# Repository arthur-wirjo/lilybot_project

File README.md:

## Lilybot: Omnidirectional Robot with LiDAR-Based Navigation

A custom omnidirectional mobile robot combining ESP32-S3 firmware, micro-ROS, and ROS 2 Nav2 for autonomous indoor navigation.

## Overview

Lilybot is a personal robotics project built to explore the full stack of an autonomous robot from scratch, from mechanical design and PCB design to embedded motor control and ROS 2 navigation.

The original motivation was simple: I wanted to build a small "smart walking table" that could help carry items around, such as bringing water or transporting cooking utensils to my dorm pantry. More importantly, this project became a way for me to learn how to build a complete autonomous robot system myself instead of only working on isolated parts.

The robot uses an ESP32-S3 for low-level control and sensing, and a Raspberry Pi 5 for higher-level ROS 2 tasks such as LiDAR processing, SLAM, localization, and navigation.

---

## Key Features

- Custom omnidirectional chassis
- Custom PCB integrating microcontroller, IMU, motor control, and encoder interfaces
- ESP32-S3-based embedded motor control firmware
- IMU and encoder feedback
- Feedforward control using a 1D lookup table with linear interpolation
- PID wheel speed control
- micro-ROS integration between ESP32-S3 and ROS 2
- LiDAR-based SLAM and Nav2 navigation on Raspberry Pi 5

---

## Hardware

### Main Components

- **Motor:** PG36-3650 geared BLDC motor, 12V rated, 1:50 reduction
- **Wheels:** Generic 75 mm omnidirectional wheels
- **IMU:** MPU6050
- **Computer:** Raspberry Pi 5 running Ubuntu 24.04
- **LiDAR:** RPLIDAR C1
- **Microcontroller:** ESP32-S3 Development Board (N16R8 variant)
- **Battery 1:** Generic 3S Li-Po battery
- **Power Distribution Board:** Generic 12V PDB with 5V output for ESP32
- **Battery 2:** Generic power bank dedicated to Raspberry Pi 5

### Custom PCB

The custom PCB includes:

- ESP32-S3 microcontroller
- IMU
- motor control outputs
- encoder feedback inputs
- two TXS0108E bidirectional level shifters

The level shifters are used because the ESP32 operates at 3.3V logic while the motor interfaces operate at 5V logic.

---

## Note on the Motor Choice

The motors used in this project are inexpensive geared BLDC motors with built-in motor drivers and encoder feedback. They are convenient for prototyping, but the velocity response is noticeably nonlinear under PWM control.

A simple PID controller alone was too slow and resulted in noticeable drift. Adding feedforward improved the response, but drift remained, especially at certain velocity ranges. I also tried a 2nd-order feedforward model with PID, which improved things further but was still not consistent enough across the full operating range.

To address this, I wrote a motor testing program to measure steady-state motor speed at different PWM duty cycles, plotted the results in a spreadsheet, and converted the data into a 1D lookup table. Linear interpolation was then used between table entries to generate the feedforward term. Combined with PID feedback, this gave the most satisfactory real-world performance.

---

## System Architecture

The system is split into two computing layers.

### ESP32-S3

The ESP32-S3 handles low-level real-time tasks:

- encoder reading
- IMU reading
- motor control loop
- odometry calculation
- micro-ROS communication
- publishing odometry-related data
- subscribing to commanded velocity data

### Raspberry Pi 5

The Raspberry Pi 5 handles high-level ROS 2 tasks:

- ROS 2 nodes
- LiDAR reading
- SLAM and localization
- Nav2 planning and control

---

## RTOS Task Structure

To keep the firmware more reliable and responsive, the ESP32-S3 uses both cores for separate responsibilities.

### Core 0: Real-Time Control

Core 0 is dedicated to the low-level control loop. Its tasks include:

- reading encoder pulse counts
- calculating odometry
- converting robot velocity targets into individual wheel targets
- running feedforward + PID wheel speed control
- updating PWM outputs to the motors

### Core 1: Communication and Sensors

Core 1 handles communication-heavy and less timing-critical tasks:

- running the micro-ROS executor
- receiving `cmd_vel` commands
- reading IMU data
- publishing IMU and odometry messages to ROS 2 over UART

This separation helped keep the control loop more stable while still maintaining communication with the Raspberry Pi.

---

## Setup

These instructions assume the Raspberry Pi 5 is running Ubuntu 24.04 and development is done over SSH.

### 1. Clone the Repository

```bash
cd ~
git clone https://github.com/arthur-wirjo/lilybot_project.git
```

---

### 2. Install ESP-IDF

Lilybot firmware is developed using ESP-IDF.

Install prerequisites:

```bash
sudo apt-get update
sudo apt-get install git wget flex bison gperf python3 python3-venv cmake ninja-build ccache libffi-dev libssl-dev dfu-util libusb-1.0-0
```

Clone ESP-IDF:

```bash
mkdir -p ~/esp
cd ~/esp
git clone -b v6.0.2 --recursive https://github.com/espressif/esp-idf.git
```

Install the toolchain:

```bash
cd ~/esp/esp-idf
./install.sh esp32
```

Export the environment:

```bash
. $HOME/esp/esp-idf/export.sh
```

Optionally, add this alias to `~/.bashrc` for convenience:

```bash
alias get_idf='. $HOME/esp/esp-idf/export.sh'
```

Then reload:

```bash
source ~/.bashrc
```

---

### 3. Flash the ESP32-S3 Firmware

In one terminal:

```bash
cd ~/lilybot_project/firmware_esp32s3/micro-ROS
idf.py flash monitor
```

---

### 4. Run the micro-ROS Agent

In another terminal:

```bash
cd ~/lilybot_project/firmware_esp32s3
docker run -it --rm -v /dev:/dev --privileged --net=host microros/micro-ros-agent:jazzy serial --dev /dev/ttyAMA0 -b 115200
```

Alternatively:

```bash
./run_microros_agent.sh
```

---

### 5. Build the ROS 2 Workspace

In another terminal:

```bash
cd ~/lilybot_project/ros2_ws
colcon build
```

---

### 6. Run the ROS 2 Stack

The main setup commands are:

```bash
ros2 launch my_robot_description rsp.launch.py
ros2 run foxglove_bridge foxglove_bridge
ros2 launch sllidar_ros2 sllidar_c1_launch.py serial_port:=/dev/ttyUSB0
ros2 run robot_localization ekf_node --ros-args --params-file src/lilybot_localization/config/ekf.yaml
ros2 launch slam_toolbox online_async_launch.py slam_params_file:=src/lilybot_localization/config/mapper_params.yaml
ros2 launch nav2_bringup bringup_launch.py use_sim_time:=False autostart:=True map:=src/lilybot_navigation/dorm_map.yaml params_file:=src/lilybot_navigation/config/custom_nav2_params.yaml
ros2 run nav2_map_server map_saver_cli -f src/lilybot_navigation/dorm_map
```

Additional setup commands are documented in the repository.

---

## Implementation Notes

This project was built solo, including:

- mechanical design
- PCB design
- embedded firmware
- control implementation
- ROS 2 integration
- robot assembly and testing

---

## Challenges and Lessons Learned

### Nonlinear Motor Behavior

One of the main challenges was achieving stable and consistent wheel speed control using low-cost motors with nonlinear PWM-to-speed behavior.

The progression was roughly:

1. PID only  
2. feedforward + PID  
3. 2nd-order feedforward + PID  
4. 1D lookup table feedforward + PID

The lookup-table-based feedforward gave the best results in practice.

### Noisy Encoder-Derived Odometry

Encoder-based odometry was noisier than expected, especially due to the characteristics of the motors and drivetrain. This made low-pass filtering important for producing more stable velocity and odometry estimates.

### Multi-Core Task Separation

Using both ESP32 cores helped keep the real-time motor control loop more reliable while offloading communication and sensor publishing to the other core.

### PCB Design Retrospective

Looking back with more hardware experience from my later DIY FOC controller project, I would have used a ground copper pour instead of manually routing ground traces point-to-point. In this case the board was simple and low power, so it still worked acceptably, but it was still not the best layout practice.

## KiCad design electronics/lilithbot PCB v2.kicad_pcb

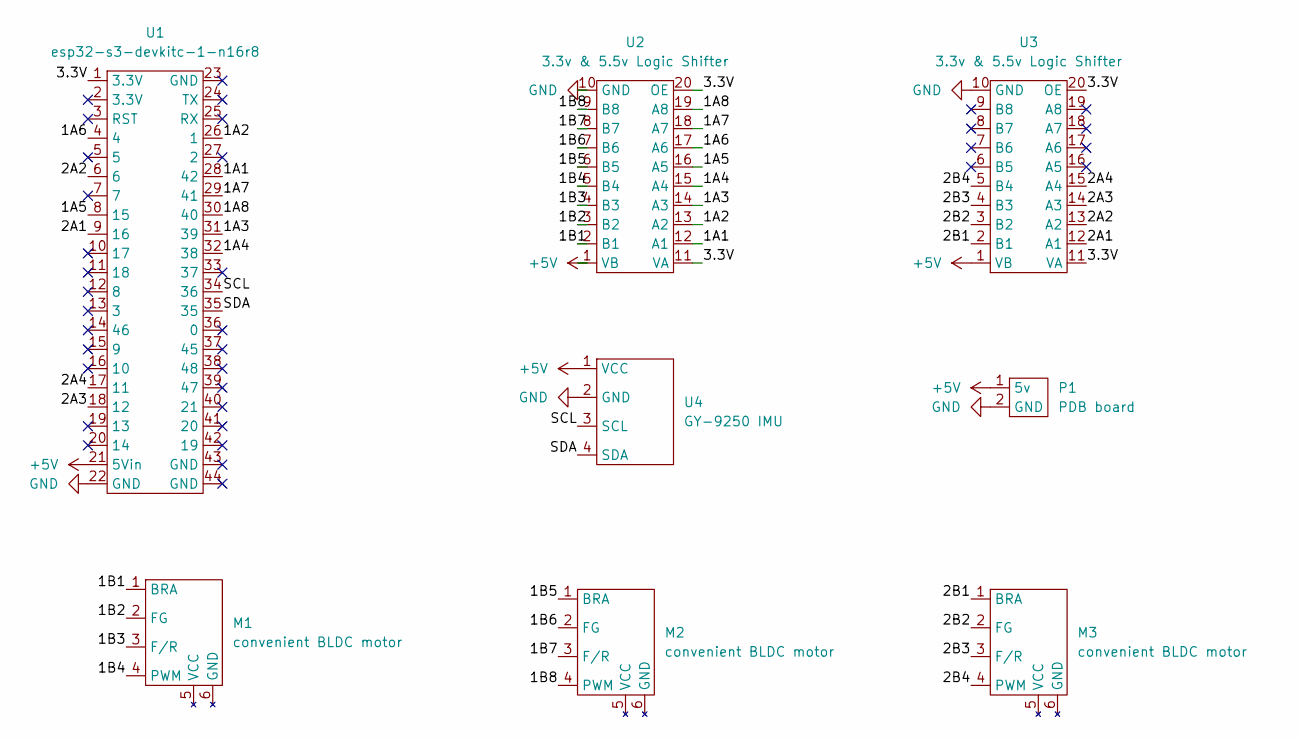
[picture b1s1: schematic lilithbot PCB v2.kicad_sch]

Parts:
M1, M2, M3: convenient BLDC motor; BDLC Motor
P1: PDB board; PDB
U1: esp32-s3-devkitc-1-n16r8
U2, U3: 3.3v & 5.5v Logic Shifter; Logic Shifter
U4: GY-9250 IMU; imu

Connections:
+5V: P1.1 (5v), U1.21 (5Vin), U2.1 (VB), U3.1 (VB), U4.1 (VCC)
/1A1: U1.28 (42), U2.12 (A1)
/1A2: U1.26 (1), U2.13 (A2)
/1A3: U1.31 (39), U2.14 (A3)
/1A4: U1.32 (38), U2.15 (A4)
/1A5: U1.8 (15), U2.16 (A5)
/1A6: U1.4, U2.17 (A6)
/1A7: U1.29 (41), U2.18 (A7)
/1A8: U1.30 (40), U2.19 (A8)
/1B1: M1.1 (BRA), U2.2 (B1)
/1B2: M1.2 (FG), U2.3 (B2)
/1B3: M1.3 (F/R), U2.4 (B3)
/1B4: M1.4 (PWM), U2.5 (B4)
/1B5: M2.1 (BRA), U2.6 (B5)
/1B6: M2.2 (FG), U2.7 (B6)
/1B7: M2.3 (F/R), U2.8 (B7)
/1B8: M2.4 (PWM), U2.9 (B8)
/2A1: U1.9 (16), U3.12 (A1)
/2A2: U1.6, U3.13 (A2)
/2A3: U1.18 (12), U3.14 (A3)
/2A4: U1.17 (11), U3.15 (A4)
/2B1: M3.1 (BRA), U3.2 (B1)
/2B2: M3.2 (FG), U3.3 (B2)
/2B3: M3.3 (F/R), U3.4 (B3)
/2B4: M3.4 (PWM), U3.5 (B4)
/3.3V: U1.1 (3.3V), U2.11 (VA), U2.20 (OE), U3.11 (VA), U3.20 (OE)
/SCL: U1.34 (36), U4.3 (SCL)
/SDA: U1.35, U4.4 (SDA)
GND: P1.2 (GND), U1.22 (GND), U2.10 (GND), U3.10 (GND), U4.2 (GND)

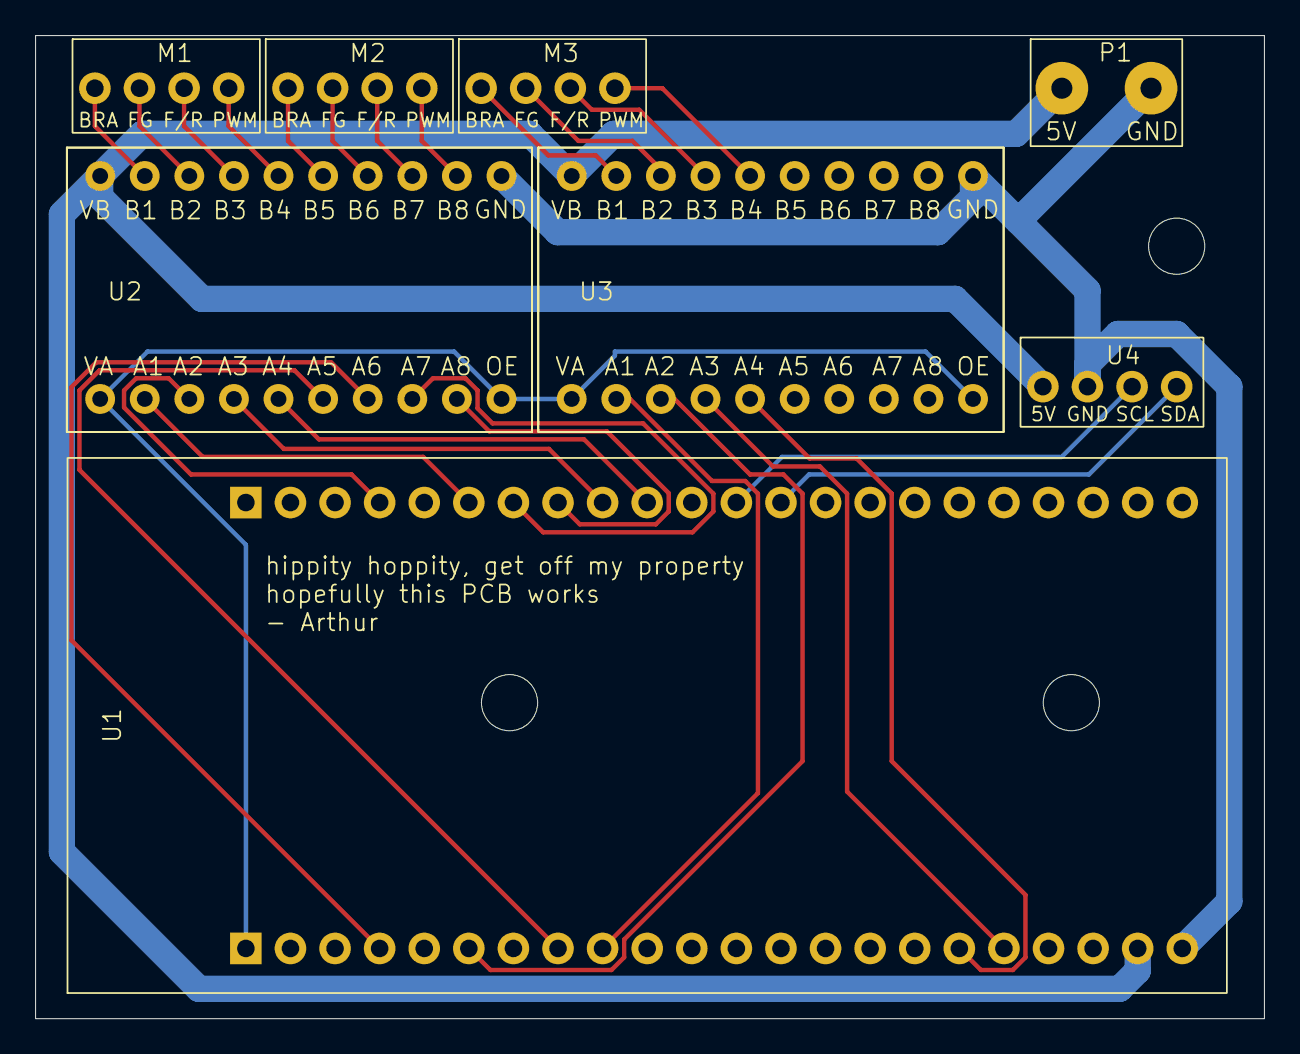
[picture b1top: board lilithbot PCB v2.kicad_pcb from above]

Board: 2 copper layers, 70.0 x 56.0 mm, 8 parts (0 on the bottom side), 29 nets.

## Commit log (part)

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2026-03-09 Vendor micro_ros_espidf_component
2026-03-09 fixed IMU pubishing issue because of incorrect bracketing in while loop
2026-03-10 removed old project for testing usb serial in micro-ROS but now uart is used so its not needed
2026-03-10 making a new esp-idf project for testing motor
2026-03-11 finsihed motor tester and its working perfectly and command is sent using uart initally for micro-ROS
2026-03-15 motor control part in progree, editing motor_tester.c to check for encoder and max wheel speed
2026-03-20 added and fixed motor_tester
2026-03-20 finished adding motor_control to micro-ROS, will test and readjust later
2026-04-08 fixed bugs for motor control task
2026-04-08 stop tracking build directories
2026-04-08 added gitignore for build directories
2026-04-15 fixed minor bug and tested the motor. works but very jiterry and innacurate
2026-04-16 added feedforward addition control, low-pass filter for odometry, derivative-on-measurement for pid
2026-04-26 added bug fixes and added ramp speed to minimize drift, though it is still very present so will have to work on that. at least it can move as it sort of supposed to.
2026-05-02 removed feedforward control to test if its better without
2026-05-04 edited motor_tester so that it detects rising and falling edge for better encoder feedback for calibration
2026-05-27 successfully fixed drifting problem by reducing the max speed and adding anti-windup and tuning PID and adding feedforward contro. currently there is a huge acceleration in the beginning leading to s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
2026-05-31 added ramp speed for less intial drift due to diffierent accelerations
2026-06-03 added the whole thing instead of just firmware
2026-06-03 added urdf and gitignores
2026-06-05 permanently added configured micro_ros_espidf_component and gitignore dependecies
2026-06-05 added extra gitignore for build and install directory inside micro-ros component
2026-06-05 fixed .gitignore file for dependecies.lock
2026-06-06 added second order feedforward control for better motor control
2026-06-06 added 1D lookup table with linear interpolation for better feedforward reponse motor control
2026-06-15 added ros2 packages for URDF, LiDAR, EKF and SLAM. Next job is to fix the orientation of odometry of micro-ROS to match the orientation of LiDAR
2026-06-15 fixed the orientation conflict between IMU and LiDAR for odometry and localization
2026-06-17 successfully implemented slam_toolbox. will work on navigation next
2026-06-18 added navigation with edited custom param file, will test soon
